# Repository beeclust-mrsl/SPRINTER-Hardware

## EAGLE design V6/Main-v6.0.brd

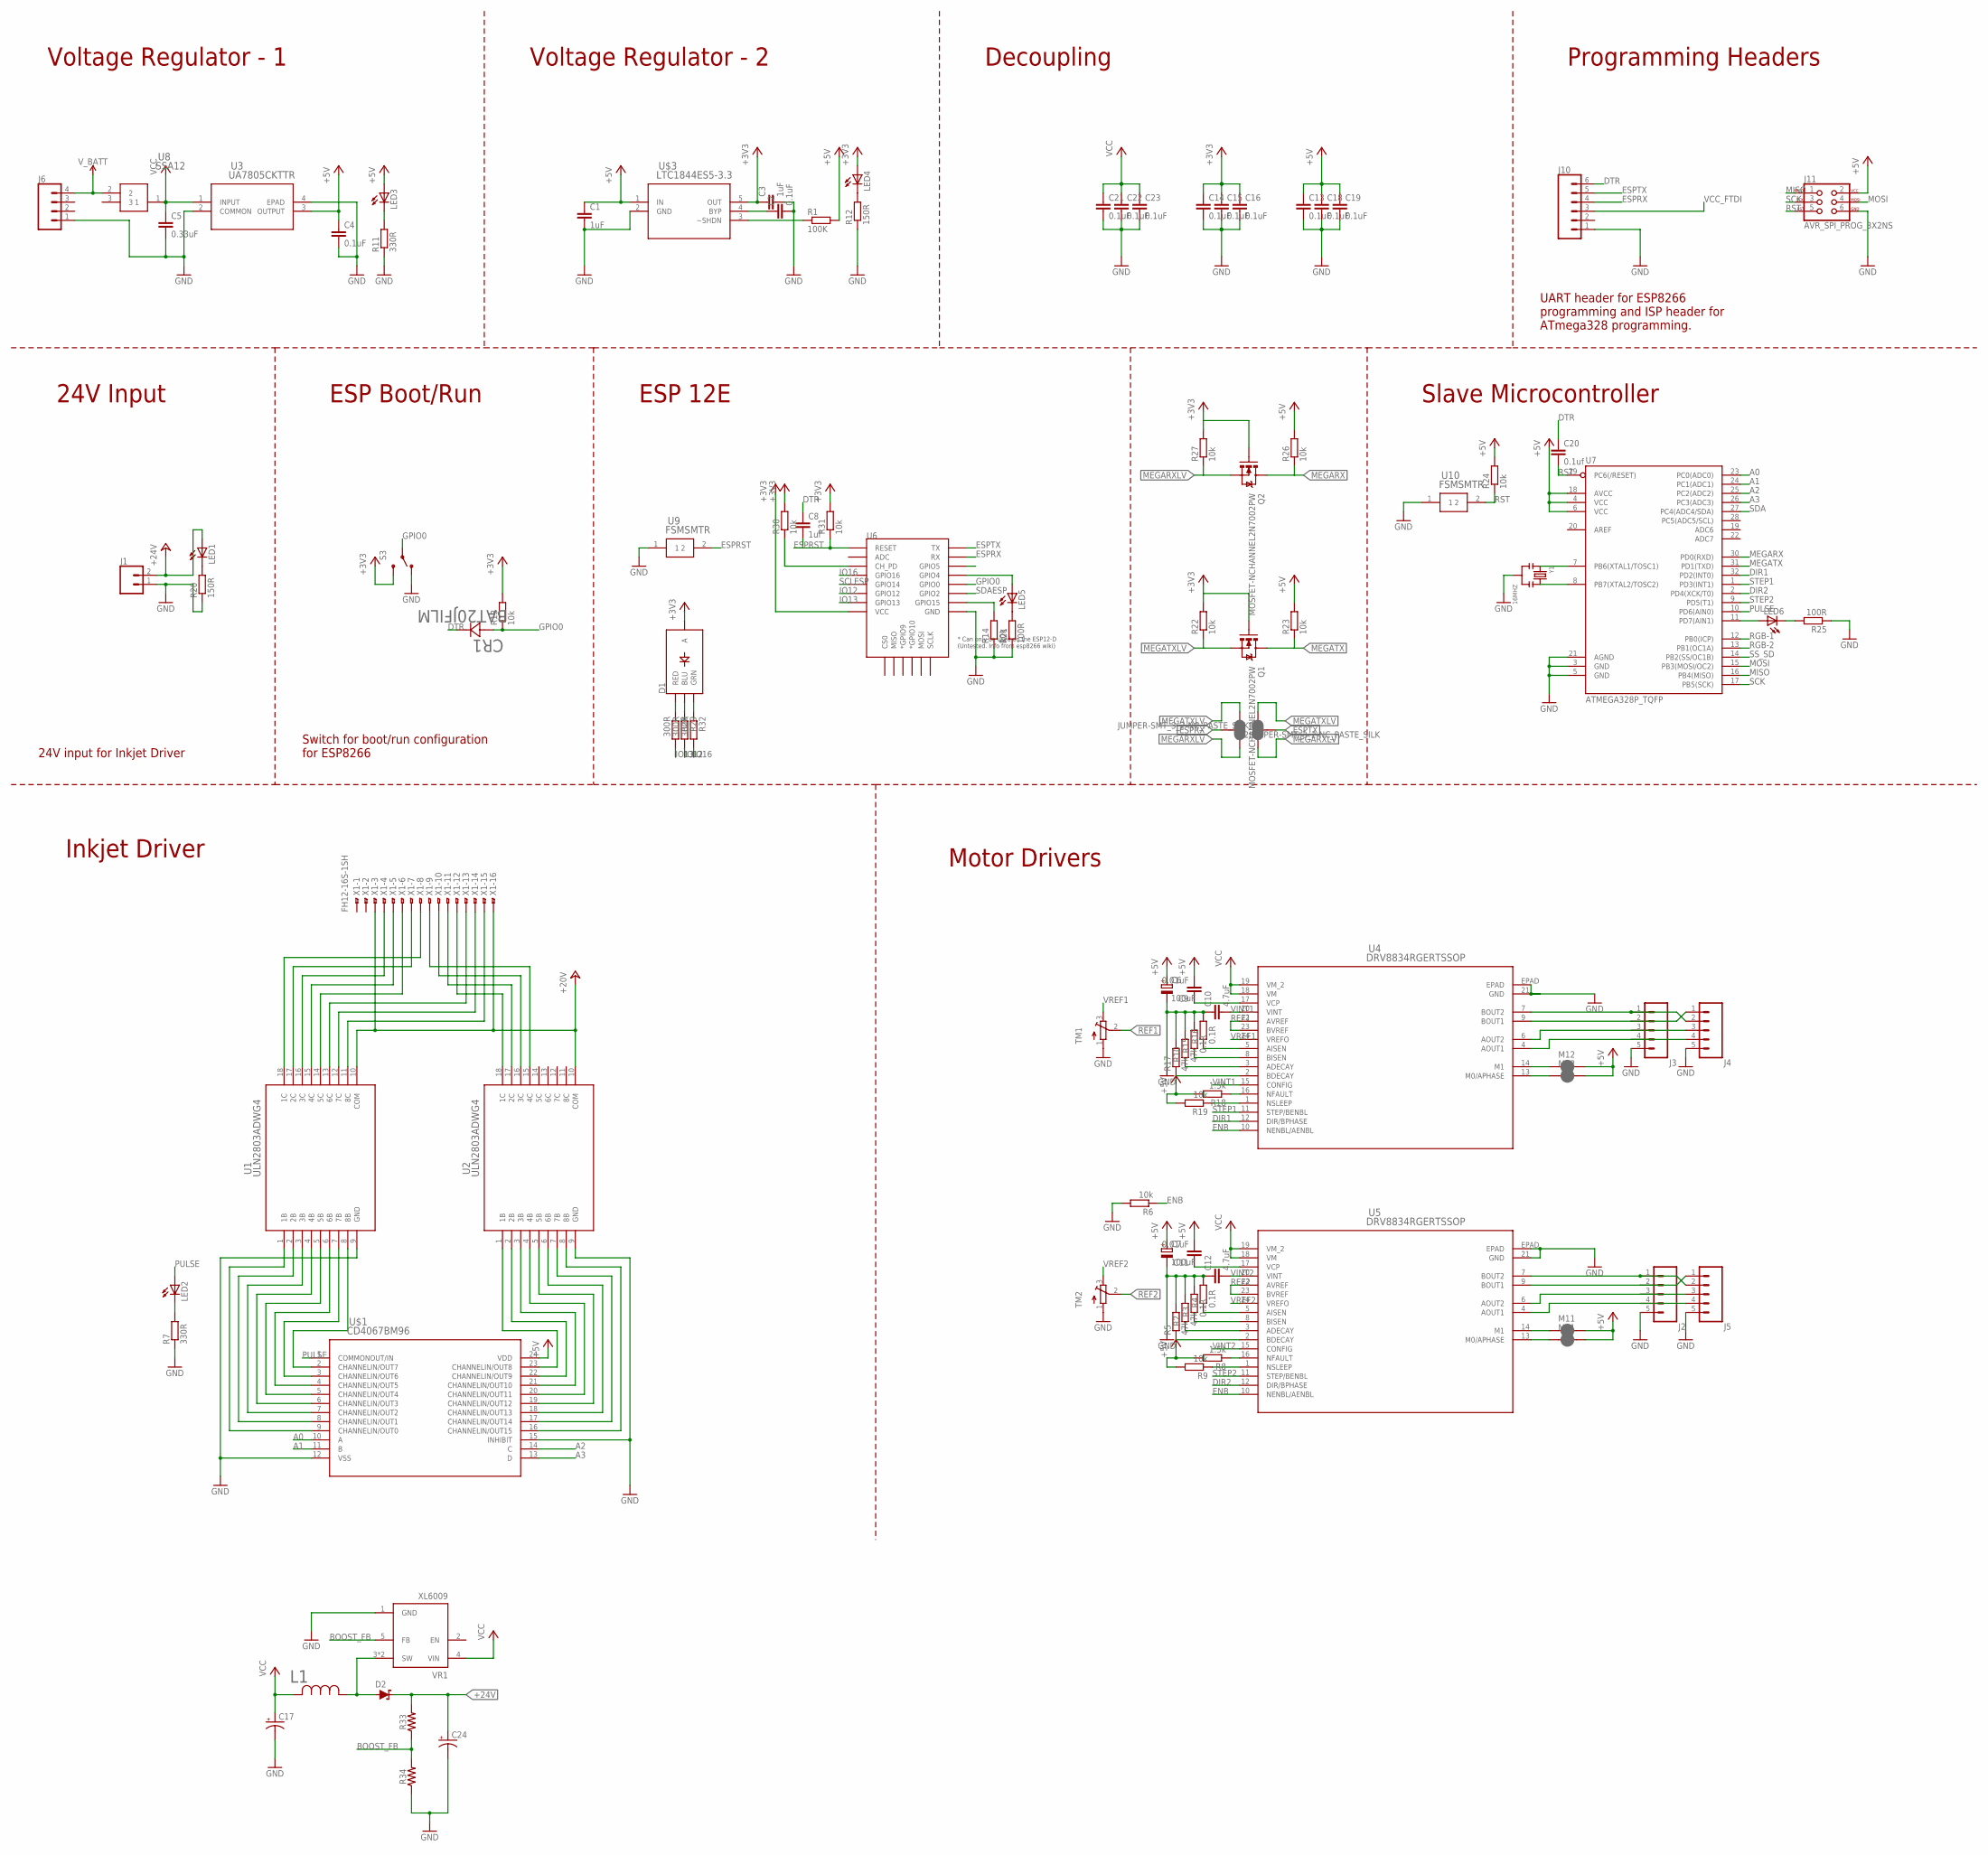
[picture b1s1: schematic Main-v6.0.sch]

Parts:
C1, C3: 1uF; C0603
C2, C4, C13, C14, C15, C16, C18, C19, C21, C22, C23: 0.1uF; C0603
C5: 0.33uF; C0603
C6, C7: 100uF; E5-5
C8: 1uf; C0603
C9, C11: 0.01uF; C0603K
C10, C12: 4.7uF; C0603K
C17: 220uF; PANASONIC_G
C20: 0.1uf; C0603
C24: 100uF; PANASONIC_D
CR1: BAT20JFILM; SOD-323
D1: LED-RGB-CASMD; LED-TRICOLOR-SMD
D2: 3A/40V/500mV; SMA-DIODE
J1: CONN_02; 1X02
J2, J3, J4, J5: CONN_05; 1X05
J6: CONN_04; 1X04
J10: CONN_06NO_SILK_NO_POP; 1X06_NO_SILK
J11: AVR_SPI_PROG_3X2NS; 2X3-NS
JP1, JP2: JUMPER-SMT_3_2-NC_PASTE_SILK; SMT-JUMPER_3_2-NC_PASTE_SILK
L1: SRR1210-680M; IND_BOURNS_SRR1210
LED1, LED2, LED3, LED4, LED5, LED6: LEDSML0603; SML0603
M01, M02, M11, M12: JUMPER-SMT_2_NC_PASTE_SILK; SMT-JUMPER_2_NC_PASTE_SILK
Q1, Q2: MOSFET-NCHANNEL2N7002PW; SOT323
R1: 100K; R0603
R2, R5, R10, R17: 47k; R0402
R3, R4, R15, R16: 0.1R; R0402
R6, R9, R19: 10k; R0402
R7, R11: 330R; R0603
R8, R18: 1.5k; R0402
R12, R20: 150R; R0603
R13, R14, R22, R23, R24, R26, R27, R30, R31: 10k; R0603
R21, R25: 100R; R0603
R28, R29, R32: 300R; R0603
R33, R34: 0603
S3: SWITCH-SPDT-SMD-A; SWITCH-SPST-SMD-A
TM1, TM2: TRIMPOTTC33X; TC33X
U1, U2: ULN2803ADWG4; DW18
U3: UA7805CKTTR; KTT3_6P22X6P6
U4, U5: DRV8834RGERTSSOP; PWP_24
U6: ESP12ESMD; ESP12E-SMD
U7: ATMEGA328P_TQFP; TQFP32-08
U8: SSA12; SWSIP3-P98
U9, U10: FSMSMTR; SWITCH_FSMSMTR
U$1: CD4067BM96; DW24
U$3: LTC1844ES5-3.3; TSOT-23_S5
VR1: XL6009; DPAK170P1435X465-6N
X1: FH12-16S-1SH
Y1: 16MHZ; X3-SMD-3.6X1.3X0.8MM

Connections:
+3V3: C3.1, C14.1, C15.1, C16.1, D1.A, LED4.A, Q1.1 (G), Q2.1 (G), R13.2, R22.2, R27.2, R30.2, R31.2, S3.3 (S), U6.VCC, U$3.5 (OUT)
+5V: C1.1, C4.1, C6.+, C7.+, C9.2, C11.2, C13.1, C18.1, C19.1, J11.2, LED3.A, M01.2, M02.2, M11.2, M12.2, R1.2, R8.2, R9.2, R18.2, R19.2, R23.2, R24.2, R26.2, U3.3 (OUTPUT), U7.4 (VCC), U7.6 (VCC), U7.18 (AVCC), U$1.24 (VDD), U$3.1 (IN)
+24V: C24.+, D2.C, J1.2, LED1.A, R33.2, U1.10 (COM), U2.10 (COM), X1.3, X1.16
A0: U7.23 (PC0(ADC0)), U$1.10 (A)
A1: U7.24 (PC1(ADC1)), U$1.11 (B)
A2: U7.25 (PC2(ADC2)), U$1.14 (C)
A3: U7.26 (PC3(ADC3)), U$1.13 (D)
BOOST_FB: R33.1, R34.2, VR1.5 (FB)
DIR1: U4.12 (DIR/BPHASE), U7.32 (PD2(INT0))
DIR2: U5.12 (DIR/BPHASE), U7.2 (PD4(XCK/T0))
DTR: C8.1, C20.1, CR1.1 (11), J10.6
ENB: R6.1, U4.10 (NENBL/AENBL), U5.10 (NENBL/AENBL)
ESPRST: C8.2, R31.1, U6.RESET, U9.2
ESPRX: J10.4, JP1.2, U6.RXD0 (RX)
ESPTX: J10.5, JP2.2, U6.TXD0 (TX)
GND: C1.2, C2.2, C3.2, C4.2, C5.2, C6.-, C7.-, C10.1, C12.1, C13.2, C14.2, C15.2, C16.2, C17.-, C18.2, C19.2, C21.2, C22.2, C23.2, C24.-, J1.1, J2.5, J3.5, J4.5, J5.5, J6.1, J10.1, J11.6, R2.2, R3.2, R4.2, R5.2, R6.2, R7.1, R10.2, R11.1, R12.1, R14.1, R15.2, R16.2, R17.2, R20.1, R21.1, R25.1, R34.1, S3.1 (O), TM1.1 (A), TM2.1 (A), U1.9 (GND), U2.9 (GND), U3.2 (COMMON), U3.4 (EPAD), U4.21 (GND), U4.EPAD, U5.21 (GND), U5.EPAD, U6.GND, U7.3 (GND), U7.5 (GND), U7.21 (AGND), U9.1, U10.1, U$1.12 (VSS), U$1.15 (INHIBIT), U$3.2 (GND), VR1.1 (GND), Y1.2
GPIO0: CR1.2 (22), R13.1, S3.2, U6.GPIO0
IO12: R29.2, U6.GPIO12
IO13: R28.2, U6.GPIO13
IO16: R32.2, U6.GPIO16
MEGARX: Q2.3 (D), R26.1, U7.30 (PD0(RXD))
MEGARXLV: JP1.3, JP2.1, Q2.2 (S), R27.1
MEGATX: Q1.3 (D), R23.1, U7.31 (PD1(TXD))
MEGATXLV: JP1.1, JP2.3, Q1.2 (S), R22.1
MISO: J11.1, U7.16 (PB4(MISO))
MOSI: J11.4, U7.15 (PB3(MOSI/OC2))
unnamed: D2.A, L1.1, VR1.3 (SW), VR1.6 (SW)
unnamed: U1.8 (8B), U$1.2 (CHANNELIN/OUT7)
unnamed: U1.7 (7B), U$1.3 (CHANNELIN/OUT6)
unnamed: U1.6 (6B), U$1.4 (CHANNELIN/OUT5)
unnamed: U1.5 (5B), U$1.5 (CHANNELIN/OUT4)
unnamed: U1.4 (4B), U$1.6 (CHANNELIN/OUT3)
unnamed: U1.3 (3B), U$1.7 (CHANNELIN/OUT2)
unnamed: U1.2 (2B), U$1.8 (CHANNELIN/OUT1)
unnamed: U1.1 (1B), U$1.9 (CHANNELIN/OUT0)
unnamed: U2.1 (1B), U$1.23 (CHANNELIN/OUT8)
unnamed: U2.2 (2B), U$1.22 (CHANNELIN/OUT9)
unnamed: U2.3 (3B), U$1.21 (CHANNELIN/OUT10)
unnamed: U2.4 (4B), U$1.20 (CHANNELIN/OUT11)
unnamed: U2.5 (5B), U$1.19 (CHANNELIN/OUT12)
unnamed: U2.6 (6B), U$1.18 (CHANNELIN/OUT13)
unnamed: J3.1, J4.2, U4.7 (BOUT2)
unnamed: J3.2, J4.1, U4.9 (BOUT1)
unnamed: J3.3, J4.3, U4.6 (AOUT2)
unnamed: J3.4, J4.4, U4.4 (AOUT1)
unnamed: U1.11 (8C), X1.15
unnamed: U1.12 (7C), X1.14
unnamed: U1.13 (6C), X1.13
unnamed: U1.14 (5C), X1.6
unnamed: U1.15 (4C), X1.5
unnamed: U1.16 (3C), X1.4
unnamed: U1.17 (2C), X1.7
unnamed: U1.18 (1C), X1.8
unnamed: U2.8 (8B), U$1.16 (CHANNELIN/OUT15)
unnamed: U2.18 (1C), X1.12
unnamed: U2.17 (2C), X1.11
unnamed: U2.16 (3C), X1.10
unnamed: U2.15 (4C), X1.9
unnamed: U2.7 (7B), U$1.17 (CHANNELIN/OUT14)
unnamed: J2.1, J5.2, U5.7 (BOUT2)
unnamed: J2.2, J5.1, U5.9 (BOUT1)
unnamed: C2.1, U$3.4 (BYP)
unnamed: R1.1, U$3.3 (~SHDN)
unnamed: J2.3, J5.3, U5.6 (AOUT2)
unnamed: J2.4, J5.4, U5.4 (AOUT1)
unnamed: C11.1, U5.17 (VCP)
unnamed: R5.1, U5.2 (BDECAY)
unnamed: R2.1, U5.3 (ADECAY)
unnamed: LED2.C, R7.2
unnamed: R3.1, U5.8 (BISEN)
unnamed: R4.1, U5.5 (AISEN)
unnamed: R9.1, U5.1 (NSLEEP)
unnamed: R8.1, U5.16 (NFAULT)
unnamed: LED3.C, R11.2
unnamed: LED4.C, R12.2
unnamed: R30.1, U6.CH_PD
unnamed: R17.1, U4.2 (BDECAY)
unnamed: LED6.C, R25.2
unnamed: LED5.C, R21.2
unnamed: LED6.A, U7.11 (PD7(AIN1))
unnamed: U7.8 (PB7(XTAL2/TOSC2)), Y1.3
unnamed: U7.7 (PB6(XTAL1/TOSC1)), Y1.1
unnamed: D1.R (RED), R28.1
unnamed: D1.B (BLU), R29.1
unnamed: D1.G (GRN), R32.1
unnamed: R10.1, U4.3 (ADECAY)
unnamed: R15.1, U4.8 (BISEN)
unnamed: R16.1, U4.5 (AISEN)
unnamed: C9.1, U4.17 (VCP)
unnamed: R19.1, U4.1 (NSLEEP)
unnamed: R18.1, U4.16 (NFAULT)
unnamed: M01.1, U5.13 (M0/APHASE)
unnamed: M11.1, U5.14 (M1)
unnamed: M02.1, U4.13 (M0/APHASE)
unnamed: M12.1, U4.14 (M1)
unnamed: LED1.C, R20.2
unnamed: LED5.A, U6.GPIO4
unnamed: R14.2, U6.GPIO15
PULSE: LED2.A, U7.10 (PD6(AIN0)), U$1.1 (COMMONOUT/IN)
REF1: TM1.2 (S), U4.22 (AVREF), U4.23 (BVREF)
REF2: TM2.2 (S), U5.22 (AVREF), U5.23 (BVREF)
RGB-1: U7.12 (PB0(ICP))
RGB-2: U7.13 (PB1(OC1A))
RST: C20.2, J11.5, R24.1, U7.29 (PC6(/RESET)), U10.2
SCK: J11.3, U7.17 (PB5(SCK))
SCLESP: U6.GPIO14
SDA: U7.27 (PC4(ADC4/SDA))
SDAESP: U6.GPIO2
SS_SD: U7.14 (PB2(SS/OC1B))
STEP1: U4.11 (STEP/BENBL), U7.1 (PD3(INT1))
STEP2: U5.11 (STEP/BENBL), U7.9 (PD5(T1))
VCC: C5.1, C17.+, C21.1, C22.1, C23.1, L1.2, U3.1 (INPUT), U4.18 (VM), U4.19 (VM_2), U5.18 (VM), U5.19 (VM_2), U8.1, VR1.4 (VIN)
VCC_FTDI: J10.3
VINT1: C10.2, U4.15 (CONFIG), U4.20 (VINT)
VINT2: C12.2, U5.15 (CONFIG), U5.20 (VINT)
VREF1: TM1.3 (E), U4.24 (VREFO)
VREF2: TM2.3 (E), U5.24 (VREFO)
V_BATT: J6.4, U8.2

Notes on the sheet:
Inkjet Driver
24V Input
ESP Boot/Run
ESP 12E
Slave Microcontroller
Voltage Regulator - 1
Voltage Regulator - 2
Decoupling
Programming Headers
Motor Drivers
UART header for ESP8266 programming and ISP header for ATmega328 programming.
Switch for boot/run configuration for ESP8266
24V input for Inkjet Driver

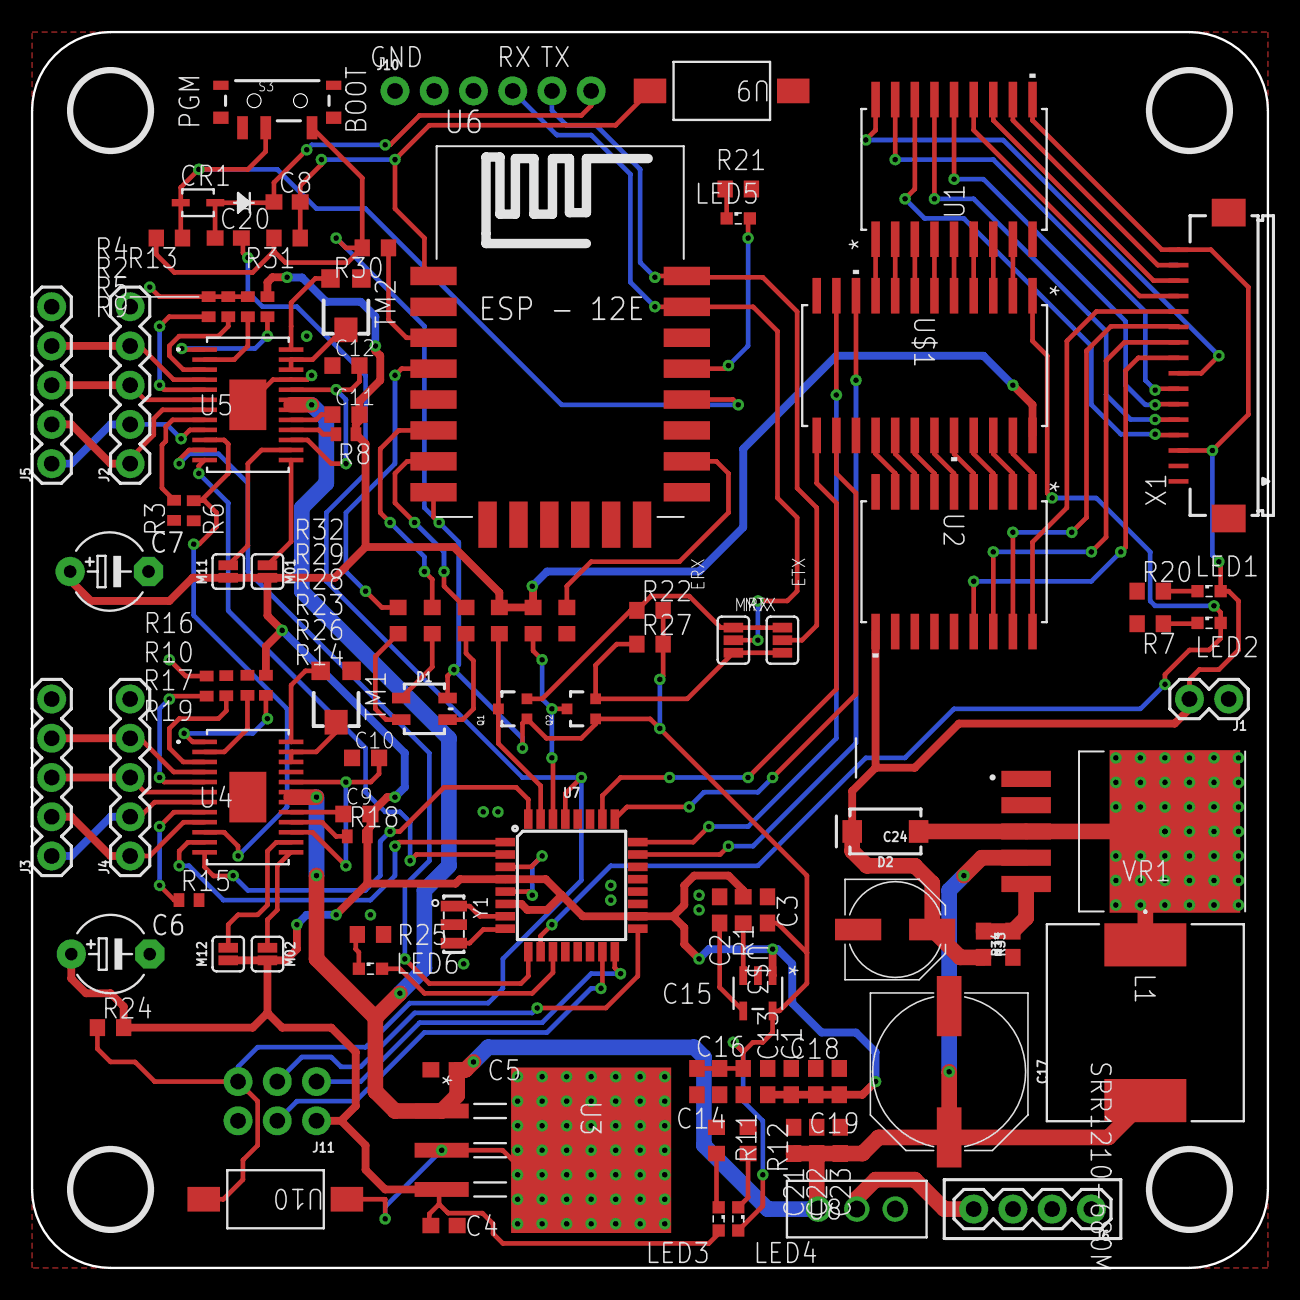
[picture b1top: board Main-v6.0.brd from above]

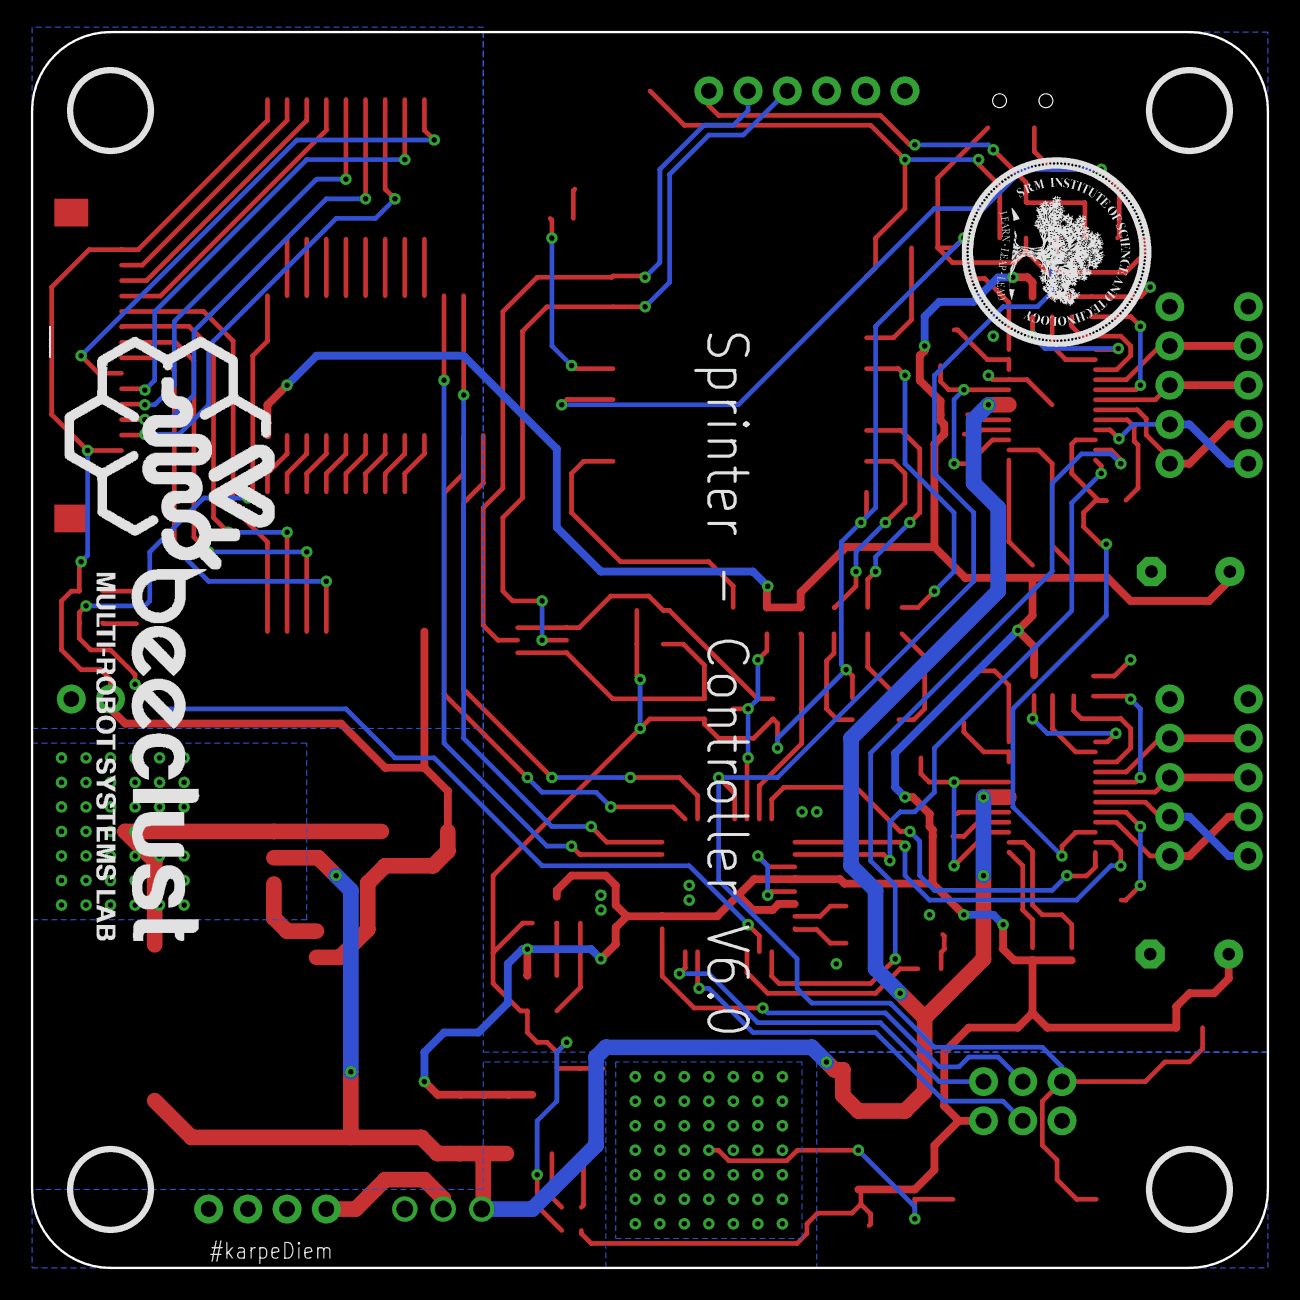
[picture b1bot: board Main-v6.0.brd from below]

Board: 2 copper layers, 80.0 x 80.0 mm, 104 parts (2 on the bottom side), 111 nets.

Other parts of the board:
U$2: LOGO-L
U$4: SRM-LOGO-M

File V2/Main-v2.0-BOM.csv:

"Qty";"Value";"Device";"Package";"Parts";"Description";"";
"1";"";"255SB";"255SB";"S1";"SLIDING SWITCH";"";
"4";"";"C-EUC0603K";"C0603K";"0.01UF, 0.01UF1, 4.7UF, 4.7UF1";"CAPACITOR, European symbol";"";
"5";"";"CONN_02";"1X02";"J1, J6, J7, J8, J9";"Multi connection point. Often used as Generic Header-pin footprint for 0.1 inch spaced/style header connections";"";
"4";"";"CONN_04";"1X04";"J2, J3, J4, J5";"Multi connection point. Often used as Generic Header-pin footprint for 0.1 inch spaced/style header connections";"";
"2";"";"L02P";"L02P";"SV1, SV2";"AMP MT CONNECTOR";"";
"6";"";"LEDSML0603";"SML0603";"LED1, LED2, LED3, LED4, LED5, LED6";"LED";"";
"1";"";"R-EU_R0603";"R0603";"R14";"RESISTOR, European symbol";"";
"4";"0.1R";"R-EU_R0402";"R0402";"R3, R4, R15, R16";"RESISTOR, European symbol";"";
"14";"0.1uF";"C-EUC0603";"C0603";"C2, C4, C13, C14, C15, C16, C17, C18, C19, C20, C21, C22, C23, C24";"CAPACITOR, European symbol";"";
"1";"0.33uF";"C-EUC0603";"C0603";"C5";"CAPACITOR, European symbol";"";
"2";"1.5k";"R-EU_R0402";"R0402";"R8, R18";"RESISTOR, European symbol";"";
"1";"100K";"R-EU_R0603";"R0603";"R1";"RESISTOR, European symbol";"";
"2";"100uF";"CPOL-EUE5-5";"E5-5";"C6, C7";"POLARIZED CAPACITOR, European symbol";"";
"3";"10k";"R-EU_R0402";"R0402";"R6, R9, R19";"RESISTOR, European symbol";"";
"2";"150R";"R-EU_R0603";"R0603";"R12, R20";"RESISTOR, European symbol";"";
"2";"1uF";"C-EUC0603";"C0603";"C1, C3";"CAPACITOR, European symbol";"";
"3";"330R";"R-EU_R0603";"R0603";"R7, R11, R13";"RESISTOR, European symbol";"";
"4";"47k";"R-EU_R0402";"R0402";"R2, R5, R10, R17";"RESISTOR, European symbol";"";
"1";"AT24C512C-SSHD-B";"AT24C512C-SSHD-B";"8S1";"U6";"";"";
"1";"BEECLUST-LOGO";"BEECLUST-LOGO";"LOGO";"U$5";"";"";
"1";"CD4067BM96";"CD4067BM96";"DW24";"U$1";"";"";
"2";"DRV8834RGER";"DRV8834RGER";"RGE24_2P45X2P45";"U4, U5";"";"";
"1";"FH12-16S-1SH";"FH12-16S-1SH";"FH12-16S-1SH";"X1";"1mm Pitch Connectors For FPC/FFC";"";
"1";"LTC1844ES5-3.3";"LTC1844ES5-3.3";"TSOT-23_S5";"U$3";"";"";
"1";"PRO-MINI";"PRO-MINI";"PRO-MINI";"U$2";"Arduion Pro Mini Clone V1.0";"";
"1";"UA7805CKTTR";"UA7805CKTTR";"KTT3_6P22X6P6";"U3";"";"";
"2";"ULN2803ADWG4";"ULN2803ADWG4";"DW18";"U1, U2";"";"";
"1";"WIRELESS-NRF24L01";"WIRELESS-NRF24L01";"WIRELESS-NRF24L01";"M1";"2.4 GHz Wireless Module based on NRF24L01 chip";"";

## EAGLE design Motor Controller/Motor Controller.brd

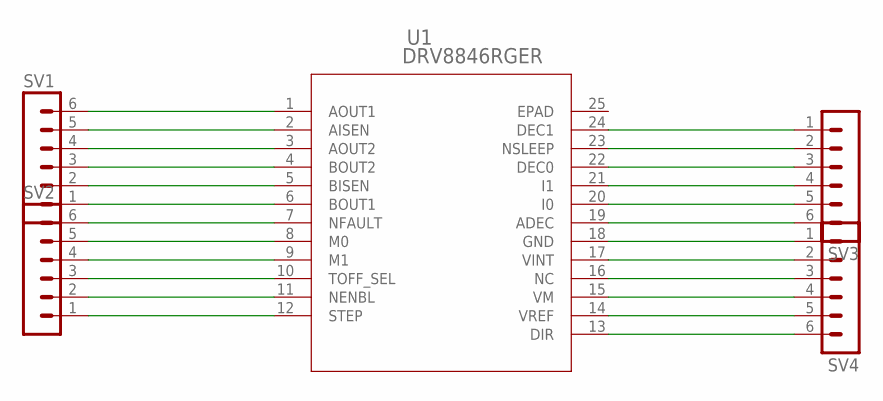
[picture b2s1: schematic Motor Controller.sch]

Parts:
SV1, SV2, SV3, SV4: MA06-1
U1: DRV8846RGER; RGE24_2P45X2P45

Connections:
unnamed: SV1.6, U1.1 (AOUT1)
unnamed: SV1.5, U1.2 (AISEN)
unnamed: SV1.4, U1.3 (AOUT2)
unnamed: SV1.3, U1.4 (BOUT2)
unnamed: SV1.1, U1.6 (BOUT1)
unnamed: SV1.2, U1.5 (BISEN)
unnamed: SV2.6, U1.7 (NFAULT)
unnamed: SV2.5, U1.8 (M0)
unnamed: SV2.4, U1.9 (M1)
unnamed: SV2.3, U1.10 (TOFF_SEL)
unnamed: SV2.2, U1.11 (NENBL)
unnamed: SV2.1, U1.12 (STEP)
unnamed: SV4.6, U1.13 (DIR)
unnamed: SV4.5, U1.14 (VREF)
unnamed: SV4.4, U1.15 (VM)
unnamed: SV4.3, U1.16 (NC)
unnamed: SV4.2, U1.17 (VINT)
unnamed: SV4.1, U1.18 (GND)
unnamed: SV3.6, U1.19 (ADEC)
unnamed: SV3.5, U1.20 (I0)
unnamed: SV3.4, U1.21 (I1)
unnamed: SV3.3, U1.22 (DEC0)
unnamed: SV3.2, U1.23 (NSLEEP)
unnamed: SV3.1, U1.24 (DEC1)

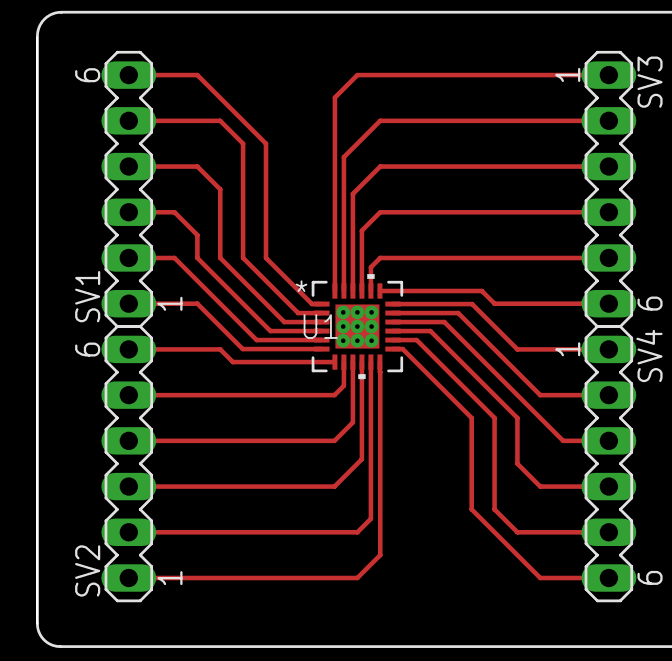
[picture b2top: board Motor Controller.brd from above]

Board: 2 copper layers, 5 parts (0 on the bottom side), 24 nets.

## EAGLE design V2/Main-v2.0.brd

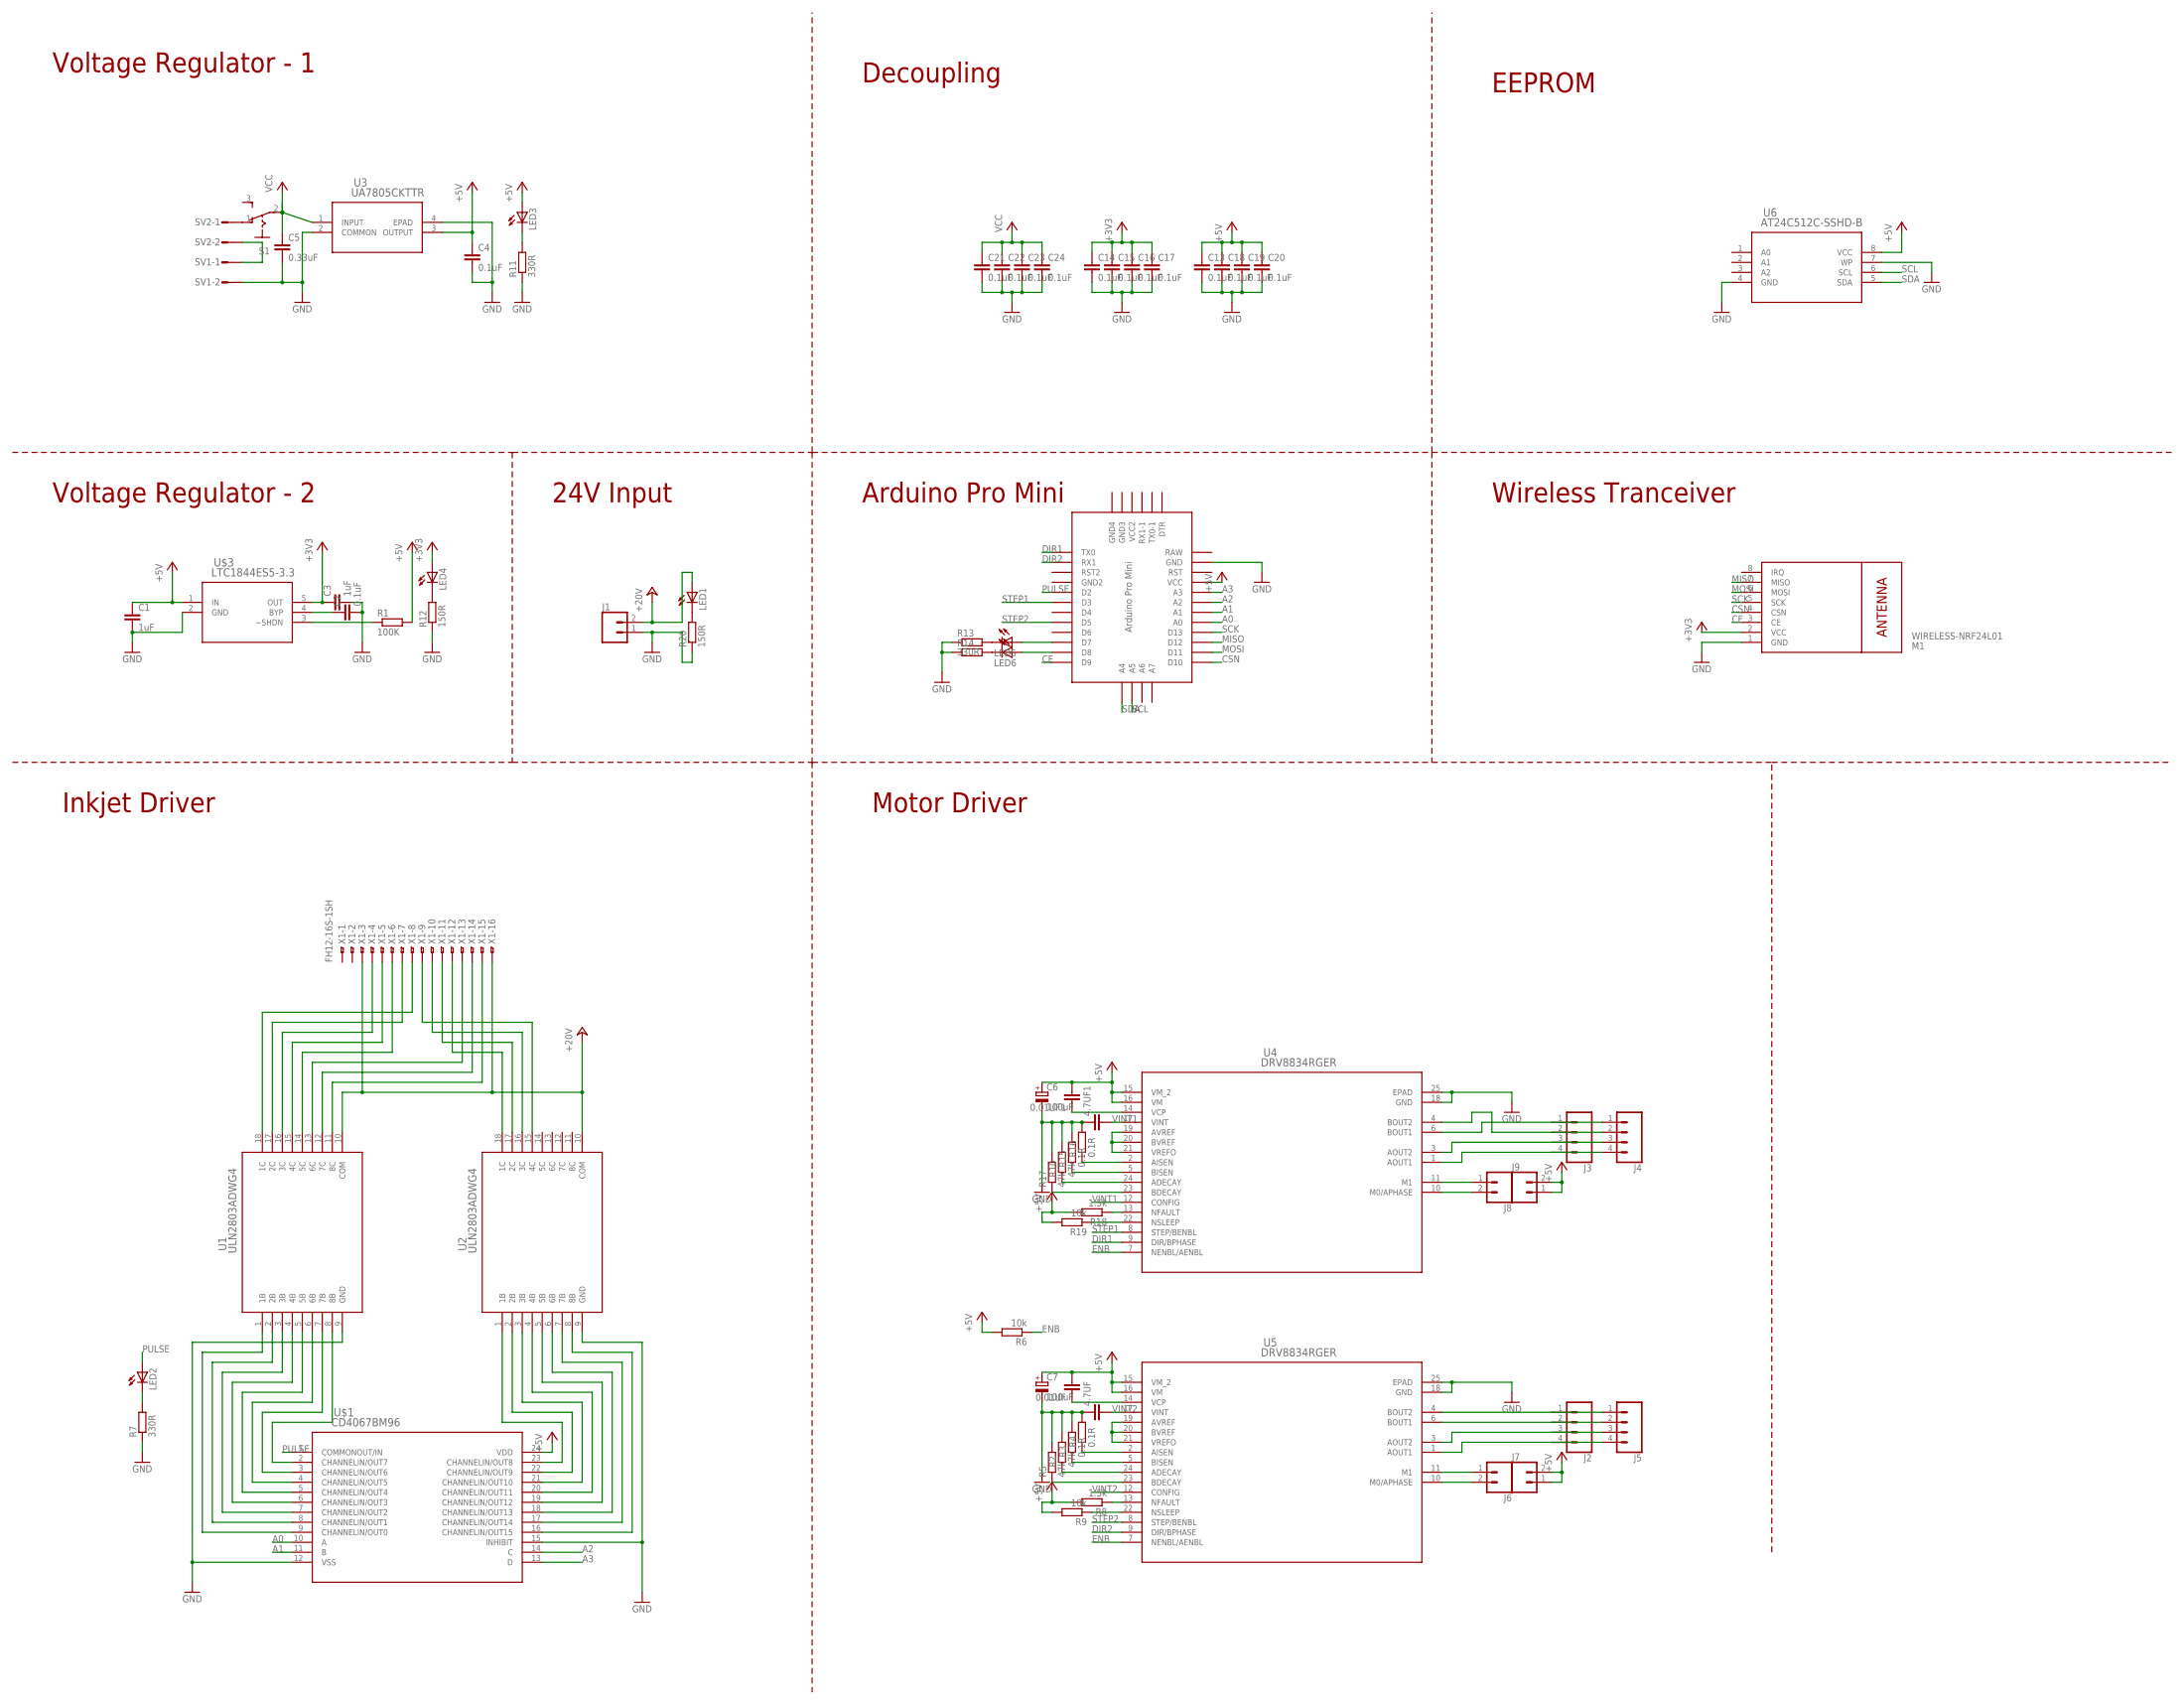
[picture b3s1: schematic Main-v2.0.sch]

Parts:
0.01UF, 0.01UF1, 4.7UF, 4.7UF1: C-EUC0603K; C0603K
C1, C3: 1uF; C0603
C2, C4, C13, C14, C15, C16, C17, C18, C19, C20, C21, C22, C23, C24: 0.1uF; C0603
C5: 0.33uF; C0603
C6, C7: 100uF; E5-5
J1, J6, J7, J8, J9: CONN_02; 1X02
J2, J3, J4, J5: CONN_04; 1X04
LED1, LED2, LED3, LED4, LED5, LED6: LEDSML0603; SML0603
M1: WIRELESS-NRF24L01
R1: 100K; R0603
R2, R5, R10, R17: 47k; R0402
R3, R4, R15, R16: 0.1R; R0402
R6, R9, R19: 10k; R0402
R7, R11, R13: 330R; R0603
R8, R18: 1.5k; R0402
R12, R20: 150R; R0603
R14: R-EU_R0603; R0603
S1: 255SB
SV1, SV2: L02P
U1, U2: ULN2803ADWG4; DW18
U3: UA7805CKTTR; KTT3_6P22X6P6
U4, U5: DRV8834RGER; RGE24_2P45X2P45
U6: AT24C512C-SSHD-B; 8S1
U$1: CD4067BM96; DW24
U$2: PRO-MINI
U$3: LTC1844ES5-3.3; TSOT-23_S5
U$5: BEECLUST-LOGO; LOGO
X1: FH12-16S-1SH

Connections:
+3V3: C3.1, C14.1, C15.1, C16.1, C17.1, LED4.A, M1.2 (VCC), U$3.5 (OUT)
+5V: 0.01UF.2, 0.01UF1.2, C1.1, C4.1, C6.+, C7.+, C13.1, C18.1, C19.1, C20.1, J7.1, J7.2, J9.1, J9.2, LED3.A, R1.2, R6.2, R8.2, R9.2, R18.2, R19.2, U3.3 (OUTPUT), U4.15 (VM_2), U4.16 (VM), U5.15 (VM_2), U5.16 (VM), U6.8 (VCC), U$1.24 (VDD), U$2.VCC, U$3.1 (IN)
+24V: J1.2, LED1.A, U1.10 (COM), U2.10 (COM), X1.3, X1.16
A0: U$1.10 (A), U$2.A0
A1: U$1.11 (B), U$2.A1
A2: U$1.14 (C), U$2.A2
A3: U$1.13 (D), U$2.A3
CE: M1.3 (CE), U$2.D9
CSN: M1.4 (CSN), U$2.D10
DIR1: U4.9 (DIR/BPHASE), U$2.TX0
DIR2: U5.9 (DIR/BPHASE), U$2.RX1
ENB: R6.1, U4.7 (NENBL/AENBL), U5.7 (NENBL/AENBL)
GND: 4.7UF.1, 4.7UF1.1, C1.2, C2.2, C3.2, C4.2, C5.2, C6.-, C7.-, C13.2, C14.2, C15.2, C16.2, C17.2, C18.2, C19.2, C20.2, C21.2, C22.2, C23.2, C24.2, J1.1, M1.1 (GND), R2.2, R3.2, R4.2, R5.2, R7.1, R10.2, R11.1, R12.1, R13.1, R14.1, R15.2, R16.2, R17.2, R20.1, SV1.2, U1.9 (GND), U2.9 (GND), U3.2 (COMMON), U3.4 (EPAD), U4.18 (GND), U4.25 (EPAD), U5.18 (GND), U5.25 (EPAD), U6.4 (GND), U6.7 (WP), U$1.12 (VSS), U$1.15 (INHIBIT), U$2.GND, U$3.2 (GND)
MISO: M1.7 (MISO), U$2.D12
MOSI: M1.6 (MOSI), U$2.D11
unnamed: SV1.1, SV2.2
unnamed: U5.19 (AVREF), U5.20 (BVREF), U5.21 (VREFO)
unnamed: U1.8 (8B), U$1.2 (CHANNELIN/OUT7)
unnamed: U1.7 (7B), U$1.3 (CHANNELIN/OUT6)
unnamed: U1.6 (6B), U$1.4 (CHANNELIN/OUT5)
unnamed: U1.5 (5B), U$1.5 (CHANNELIN/OUT4)
unnamed: U1.4 (4B), U$1.6 (CHANNELIN/OUT3)
unnamed: U1.3 (3B), U$1.7 (CHANNELIN/OUT2)
unnamed: U1.2 (2B), U$1.8 (CHANNELIN/OUT1)
unnamed: U1.1 (1B), U$1.9 (CHANNELIN/OUT0)
unnamed: U2.1 (1B), U$1.23 (CHANNELIN/OUT8)
unnamed: U2.2 (2B), U$1.22 (CHANNELIN/OUT9)
unnamed: U2.3 (3B), U$1.21 (CHANNELIN/OUT10)
unnamed: U2.4 (4B), U$1.20 (CHANNELIN/OUT11)
unnamed: U2.5 (5B), U$1.19 (CHANNELIN/OUT12)
unnamed: U2.6 (6B), U$1.18 (CHANNELIN/OUT13)
unnamed: J3.1, J4.1, U4.6 (BOUT1)
unnamed: J3.2, J4.2, U4.4 (BOUT2)
unnamed: J3.3, J4.3, U4.3 (AOUT2)
unnamed: J3.4, J4.4, U4.1 (AOUT1)
unnamed: U1.11 (8C), X1.15
unnamed: U1.12 (7C), X1.14
unnamed: U1.13 (6C), X1.13
unnamed: U1.14 (5C), X1.6
unnamed: U1.15 (4C), X1.5
unnamed: U1.16 (3C), X1.4
unnamed: U1.17 (2C), X1.7
unnamed: U1.18 (1C), X1.8
unnamed: U2.8 (8B), U$1.16 (CHANNELIN/OUT15)
unnamed: U2.18 (1C), X1.12
unnamed: U2.17 (2C), X1.11
unnamed: U2.16 (3C), X1.10
unnamed: U2.15 (4C), X1.9
unnamed: U2.7 (7B), U$1.17 (CHANNELIN/OUT14)
unnamed: J2.1, J5.1, U5.4 (BOUT2)
unnamed: J2.2, J5.2, U5.6 (BOUT1)
unnamed: S1.1 (O), SV2.1
unnamed: C2.1, U$3.4 (BYP)
unnamed: R1.1, U$3.3 (~SHDN)
unnamed: J2.3, J5.3, U5.3 (AOUT2)
unnamed: J2.4, J5.4, U5.1 (AOUT1)
unnamed: 0.01UF.1, U5.14 (VCP)
unnamed: R5.1, U5.23 (BDECAY)
unnamed: R2.1, U5.24 (ADECAY)
unnamed: LED2.C, R7.2
unnamed: R3.1, U5.5 (BISEN)
unnamed: R4.1, U5.2 (AISEN)
unnamed: R9.1, U5.22 (NSLEEP)
unnamed: R8.1, U5.13 (NFAULT)
unnamed: LED3.C, R11.2
unnamed: LED4.C, R12.2
unnamed: LED5.C, R13.2
unnamed: U4.19 (AVREF), U4.20 (BVREF), U4.21 (VREFO)
unnamed: R17.1, U4.23 (BDECAY)
unnamed: LED6.C, R14.2
unnamed: LED5.A, U$2.D7
unnamed: LED6.A, U$2.D8
unnamed: R10.1, U4.24 (ADECAY)
unnamed: R15.1, U4.5 (BISEN)
unnamed: R16.1, U4.2 (AISEN)
unnamed: 0.01UF1.1, U4.14 (VCP)
unnamed: R19.1, U4.22 (NSLEEP)
unnamed: R18.1, U4.13 (NFAULT)
unnamed: J6.2, U5.10 (M0/APHASE)
unnamed: J6.1, U5.11 (M1)
unnamed: J8.2, U4.10 (M0/APHASE)
unnamed: J8.1, U4.11 (M1)
unnamed: LED1.C, R20.2
PULSE: LED2.A, U$1.1 (COMMONOUT/IN), U$2.D2
RAW: U$2.RAW
SCK: M1.5 (SCK), U$2.D13
SCL: U6.6 (SCL), U$2.A5
SDA: U6.5 (SDA), U$2.A4
STEP1: U4.8 (STEP/BENBL), U$2.D3
STEP2: U5.8 (STEP/BENBL), U$2.D5
VCC: C5.1, C21.1, C22.1, C23.1, C24.1, S1.2, U3.1 (INPUT)
VINT1: 4.7UF1.2, U4.12 (CONFIG), U4.17 (VINT)
VINT2: 4.7UF.2, U5.12 (CONFIG), U5.17 (VINT)

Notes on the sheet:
Inkjet Driver
Motor Driver
Voltage Regulator - 1
Voltage Regulator - 2
24V Input
Decoupling
EEPROM
Arduino Pro Mini
Wireless Tranceiver

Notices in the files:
parts and their libraries:
diy-modules: Released under the Creative Commons Attribution 4.0 International License: http://creativecommons.org/licenses/by/4.0
SparkFun-Connectors: Licensing: Creative Commons ShareAlike 4.0 International - https://creativecommons.org/licenses/by-sa/4.0
